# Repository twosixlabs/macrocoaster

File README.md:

# Macrocoaster

Thank you for picking up a macrocoaster from TwoSix Technologies!

If you weren't able to pick one up in person, [this repo](./hardware/PCB/) contains mainufacturing files to order your own board (through JLCPCB, PCBWAY, etc.)

## Why this?
We wanted to give you something useful, fun, and memorable, whether it's a neat circuit board coaster, a fun beginner-friendly soldering kit, or a powerful productivity tool :)

## Usage
The Macrocoaster has two main uses: as a coaster, and as a macropad!
### Coaster:

* Coaster 👍
### Macropad:

* A "macropad" is a (usually) small keyboard used to add functionality to or automate your regular keyboard. Each key's function is programmable, so on a press it can type entire paragraphs, change your computer volume, or hit a combination of keys together. 

* The macrocoaster is unique in that there is a knob that lets you scroll through [layers](https://keebmaker.com/pages/layers), allowing for "pages" of macro keys, instead of just 11. You can think of this like how your SHIFT key changes certain keyboard keys to something else, but instead of one modifier key (SHIFT), you have a dial!

## Feature Overview
### Hardware
* Ruler
    * Inch and mm ruler
    * Common trace widths
    * Common hole diameters
* Header references
    * Common header pitches for reference
* Cross-microcontroller compatibility
    * The macrocoaster board can use an [Arduino Pro Micro](https://www.aliexpress.us/item/3256805735375493.html), [Elite-C](https://www.boardsource.xyz/products/Elite-C_v4), [kb2040](https://www.adafruit.com/product/5302) or any other pro-micro-esque footprint board [supported by QMK](https://github.com/qmk/qmk_firmware/blob/master/docs/compatible_microcontrollers.md)
* ENIG finish - there's gold on this board! 😱
### Software
* Scrollable layers
    * The left rotary encoder scrolls through defined keyboard layers (displayed on the OLED) for a theoretical maximum of (32 layers) * (11 keys) = *_352_ custom macro keys*!
* Bindable rotary encoder
    * By default, the right rotary encoder functions as a volume knob, but can be rebound to send any keycode! (for example, scrolling the grid size in KiCAD)
* Caps-lock indicator via OLED

## BoM (Bill of Materials)
See the [interactive BoM](https://htmlpreview.github.io/?https://github.com/twosixlabs/macrocoaster/blob/main/hardware/BoM/ibom.html) :)
<!-- Note: Update link to future repo! -->

#### Required:
* Microcontroller (see [above](#hardware))
* Any full-size [Cherry MX](https://www.keychron.com/blogs/news/cherry-mechanical-switch-guide) style [keyswitches](https://www.theremingoat.com/blog/beginners-guide) work 
    * Personally, [these](https://drop.com/buy/everglide-oreo-mechanical-switches) and [these](https://divinikey.com/products/lelelab-y2k-tactile-switches) are my favorite
* I recommend [EC-11 style rotary encoders](https://www.amazon.com/uxcell-Degree-Encoder-Digital-Potentiometer/dp/B07R8JPM6D)
* I used [these diodes](https://www.amazon.com/BOJACK-Switching-IN4148-Electronic-Silicon/dp/B07Q4F3Y5W)
* Any 128x64 `SSD1306` OLED breakout with a `[GND, Vcc, SCL, SDA]` pinout works
    * I used [these](https://www.amazon.com/Hosyond-Display-Self-Luminous-Compatible-Raspberry/dp/B09C5K91H7) as the yellow lines make the layer name stand out nicely :D

#### Optional: (but highly recommended)
* Keycaps
    * Entirely your preference :)
        * [This site](https://kbdfans.com/collections/keycaps) is a great starting point
            * Check if there is a "numpad" set, if you don't want the whole keyboard
            * Sites such as [this](https://www.wasdkeyboards.com/products/keycaps/blank-keycap-singles.html) offer per-key pricing, some other sites can even print custom designs on keys!
* Rotary encoder knobs
    * There are many, many [options](https://www.amazon.com/s?k=potentiometer+knob), just make sure they fit your encoder shaft (some are semi-circles, some have knurling, etc.)
* [Rubber "feet"](https://www.amazon.com/s?k=rubber+feet)
    * This keeps the bottom of the board (with the solder blobs/THT components) from scratching up or shorting on whatever surface you have.

## Assembly
1. Liberally apply flux to the back of the board (the side with all the graphics)
2. Place your key switches (`SW1` - `SW11`) in (on the side without the rules), and solder them
3. Diodes (technically optional, if you don't care about [ghosting](https://pcbheaven.com/wikipages/How_Key_Matrices_Works/))
    * If using diodes, solder down `D1` - `D11` (in any order). Make sure the polarity is correct.
    * If not using diodes, short `D1` - `D11` with solder, wires, or leads
4. Solder both rotary encoders (`SW13`, `SW14`)
5. Solder down your controller
    * You can use the castellated pads if your controller has them, or simply use traditional headers
6. Head down to the [Programming guide](#programming) before soldering the OLED
7. Apply some kapton (or other non-conductive tape) to the bottom of the OLED
    * This prevents the OLED from shorting microcontroller pins
8. Solder down the OLED so it covers your controller
    * Note: if using headers (instead of castellated pads) to solder down your controller, you made need [tall headers](https://www.amazon.com/HiLetgo-20pcs-2-54mm-Single-Header/dp/B07R5QDL8D) or [female headers](https://www.amazon.com/Glarks-Connector-Assortment-Stackable-Breakaway/dp/B07CWSXY7P) to clear the board.
        * In the case of the kb2040, the stemma connector causes the OLED to sit at a bit of an angle, which personally I find kind of convenient.

## Programming
1. Install `qmk`
    * [QMK install guide](https://docs.qmk.fm/#/newbs_building_firmware)
        * Note: Merging the macrocoaster into qmk is underway.
        * For now
          * Define a new keyboard `qmk new-keyboard`
          * Choose last option `none of the above`
          * Choose your chip, although it doesn't matter. I selected `kb2040`
2. Download the code
    * `git clone https://github.com/twosixtech/macrocoaster && cd macrocoaster/firmware`
3. Compile and flash for your microcontroller
    * You will need to press the Flash/boot/etc. button down when loading the code for the first time (QMK will prompt you ) 
        * All later flashes can be done with the [magic-bootloader](https://github.com/qmk/qmk_firmware/blob/master/docs/feature_bootmagic.md) key :)
     * delete everything in the macrocoaster dir defined with `qmk new-keyboard` above
     * copy   `macrocoaster/firmware` into your qmk home dir and difined firmware for macrocoaster `qmk_firmware/keyboards/macrocoaster`. Like this `cp -r * ~/qmk_firmware/keyboards/macrocoaster` or similar.
    * Elite-C/Pro-micro
        * `qmk compile -kb macrocoaster -km default && qmk flash -bl dfu -km default -kb macrocoaster`
    * kb2040
        * `qmk compile -kb macrocoaster -km default && qmk flash -km default -kb macrocoaster -e CONVERT_TO=kb2040`

## Macropad Usage
By default, the macropad comes with (roughly) [this layout](./firmware/keymaps/default/keymap.c):

# Notes
To put the KB2040 into programming mode, with the USB port oriented up, hold the bottom left button down, and then press the right and release the left. As documented [here](https://golem.hu/guide/kmk-firmware/)

## Customization (WIP)
Almost all customization will be done in the [`keymap.c`](./firmware/keymaps/default/keymap.c) file.

See the [QMK docs](https://docs.qmk.fm/#/) and [QMK code](https://github.com/qmk/qmk_firmware/blob/master/docs/) for instructions/guidance, as well as the comments in `keymap.c`.
* If you toss the code, with its existing comments into ChatGPT, it does a pretty good job at helping explain :)

The bootloader can be entered by holding down the `SW4` key while the board is powered on
* Note: with the `kb2040`, entering the bootloader make take a few attempts (make sure to wait ~5s on each attempt)

_Note_: Unfortunately because of QMK is architected with macros and `#define`'s, values for things like layer #'s must be known at compile-time and not runtime, making things like automatically calculating the next/prev layer very difficult :(
For example, 
```
#define NUMBER_OF_LAYERS (sizeof(keymaps) / sizeof(keymaps[0]))

int get_next_layer(int currlayer) {
    return (currlayer + 1) % NUMBER_OF_LAYERS;
}
int get_prev_layer(int currlayer) {
    return (currlayer - 1 + NUMBER_OF_LAYERS) % NUMBER_OF_LAYERS;
}
```
is not possible. </a>

## Cases
STL/3MF files for 3D-printable cases can be found in the [cases](./hardware/Cases) folder :)

## Builds
If you feel inclined, it would be amazing if if/after you complete a macrocoaster build, you post it in the [builds](./builds) folder! I posted [my build(s)](./builds/Engineer-2) there, feel free to copy that folder and use it as a template :)

If you want to share your build, please open a PR with your setup in its own subfolder in the builds folder!

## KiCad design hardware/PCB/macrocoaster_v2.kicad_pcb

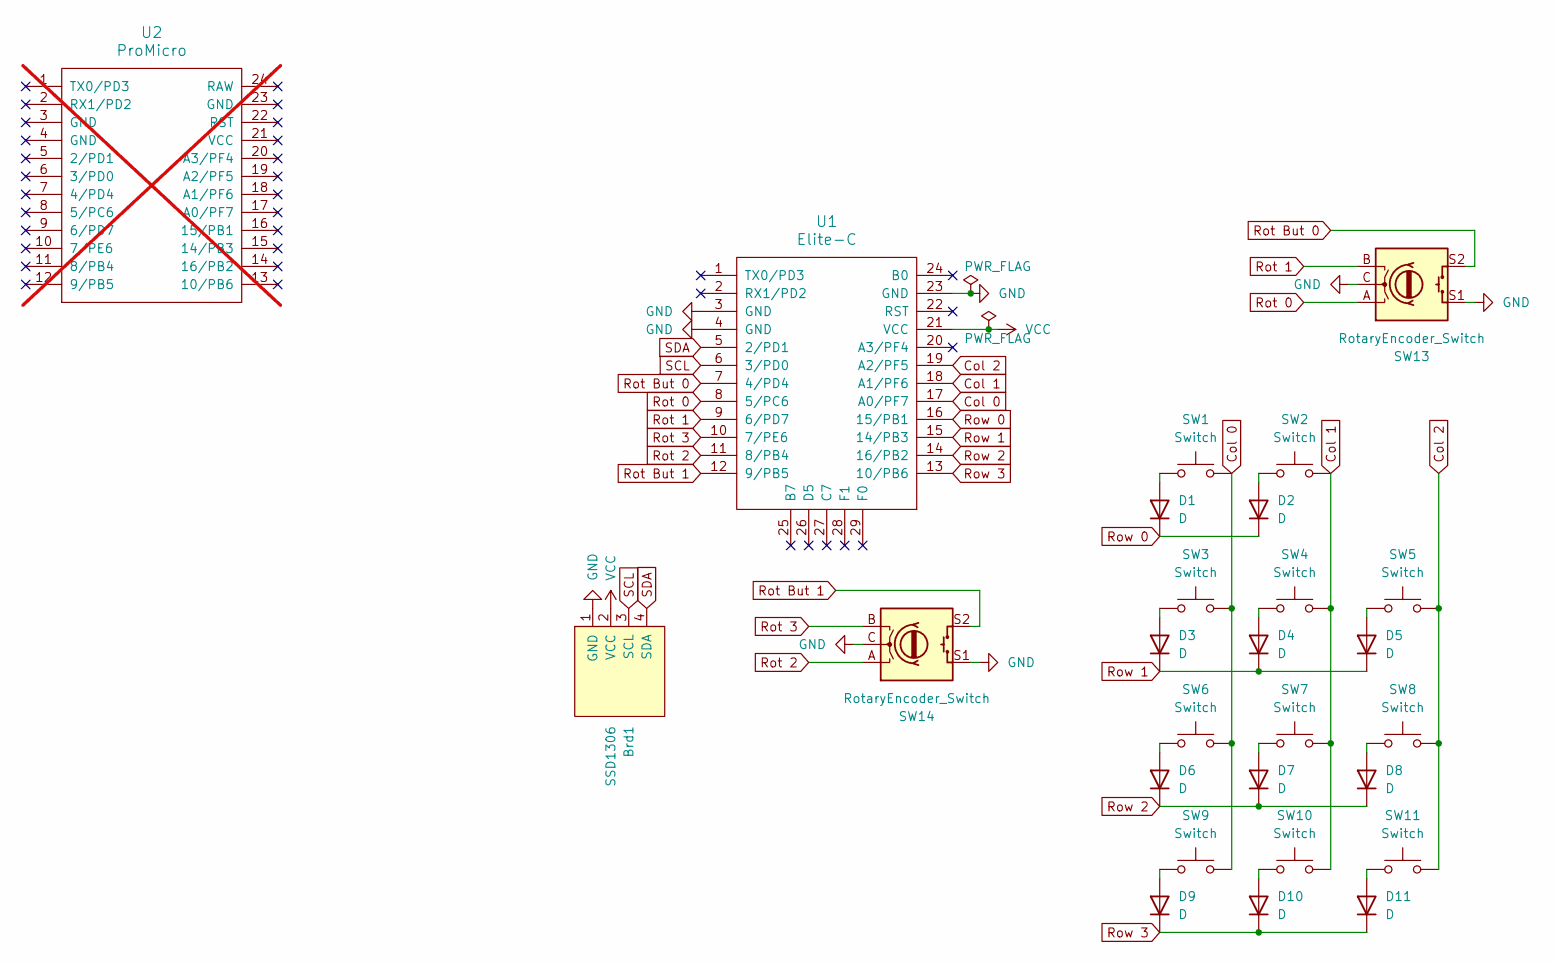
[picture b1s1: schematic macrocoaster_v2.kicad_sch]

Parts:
Brd1: SSD1306; 128x64OLED
D1, D2, D3, D4, D5, D6, D7, D8, D9, D10, D11: D; D_SOD123_axial
SW1, SW2, SW3, SW4, SW5, SW6, SW7, SW8, SW9, SW10, SW11: Switch; MX_PCB_1.00u
SW13, SW14: RotaryEncoder_Switch; RotaryEncoder_Alps_EC11E-Switch_Vertical_H20mm
U1: Elite-C; Elite-C-castellated-29pin-holes
U2: ProMicro; not fitted

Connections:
Col 0: SW1.2, SW3.2, SW6.2, SW9.2, U1.17 (A0/PF7)
Col 1: SW2.2, SW4.2, SW7.2, SW10.2, U1.18 (A1/PF6)
Col 2: SW5.2, SW8.2, SW11.2, U1.19 (A2/PF5)
GND: Brd1.1 (GND), SW13.C, SW13.S1, SW14.C, SW14.S1, U1.3 (GND), U1.4 (GND), U1.23 (GND)
unnamed: D1.2 (A), SW1.1
unnamed: D2.2 (A), SW2.1
unnamed: D3.2 (A), SW3.1
unnamed: D4.2 (A), SW4.1
unnamed: D5.2 (A), SW5.1
unnamed: D6.2 (A), SW6.1
unnamed: D7.2 (A), SW7.1
unnamed: D8.2 (A), SW8.1
unnamed: D9.2 (A), SW9.1
unnamed: D10.2 (A), SW10.1
unnamed: D11.2 (A), SW11.1
Rot 0: SW13.A, U1.8 (5/PC6)
Rot 1: SW13.B, U1.9 (6/PD7)
Rot 2: SW14.A, U1.11 (8/PB4)
Rot 3: SW14.B, U1.10 (7/PE6)
Rot But 0: SW13.S2, U1.7 (4/PD4)
Rot But 1: SW14.S2, U1.12 (9/PB5)
Row 0: D1.1 (K), D2.1 (K), U1.16 (15/PB1)
Row 1: D3.1 (K), D4.1 (K), D5.1 (K), U1.15 (14/PB3)
Row 2: D6.1 (K), D7.1 (K), D8.1 (K), U1.14 (16/PB2)
Row 3: D9.1 (K), D10.1 (K), D11.1 (K), U1.13 (10/PB6)
SCL: Brd1.3 (SCL), U1.6 (3/PD0)
SDA: Brd1.4 (SDA), U1.5 (2/PD1)
VCC: Brd1.2 (VCC), U1.21 (VCC)

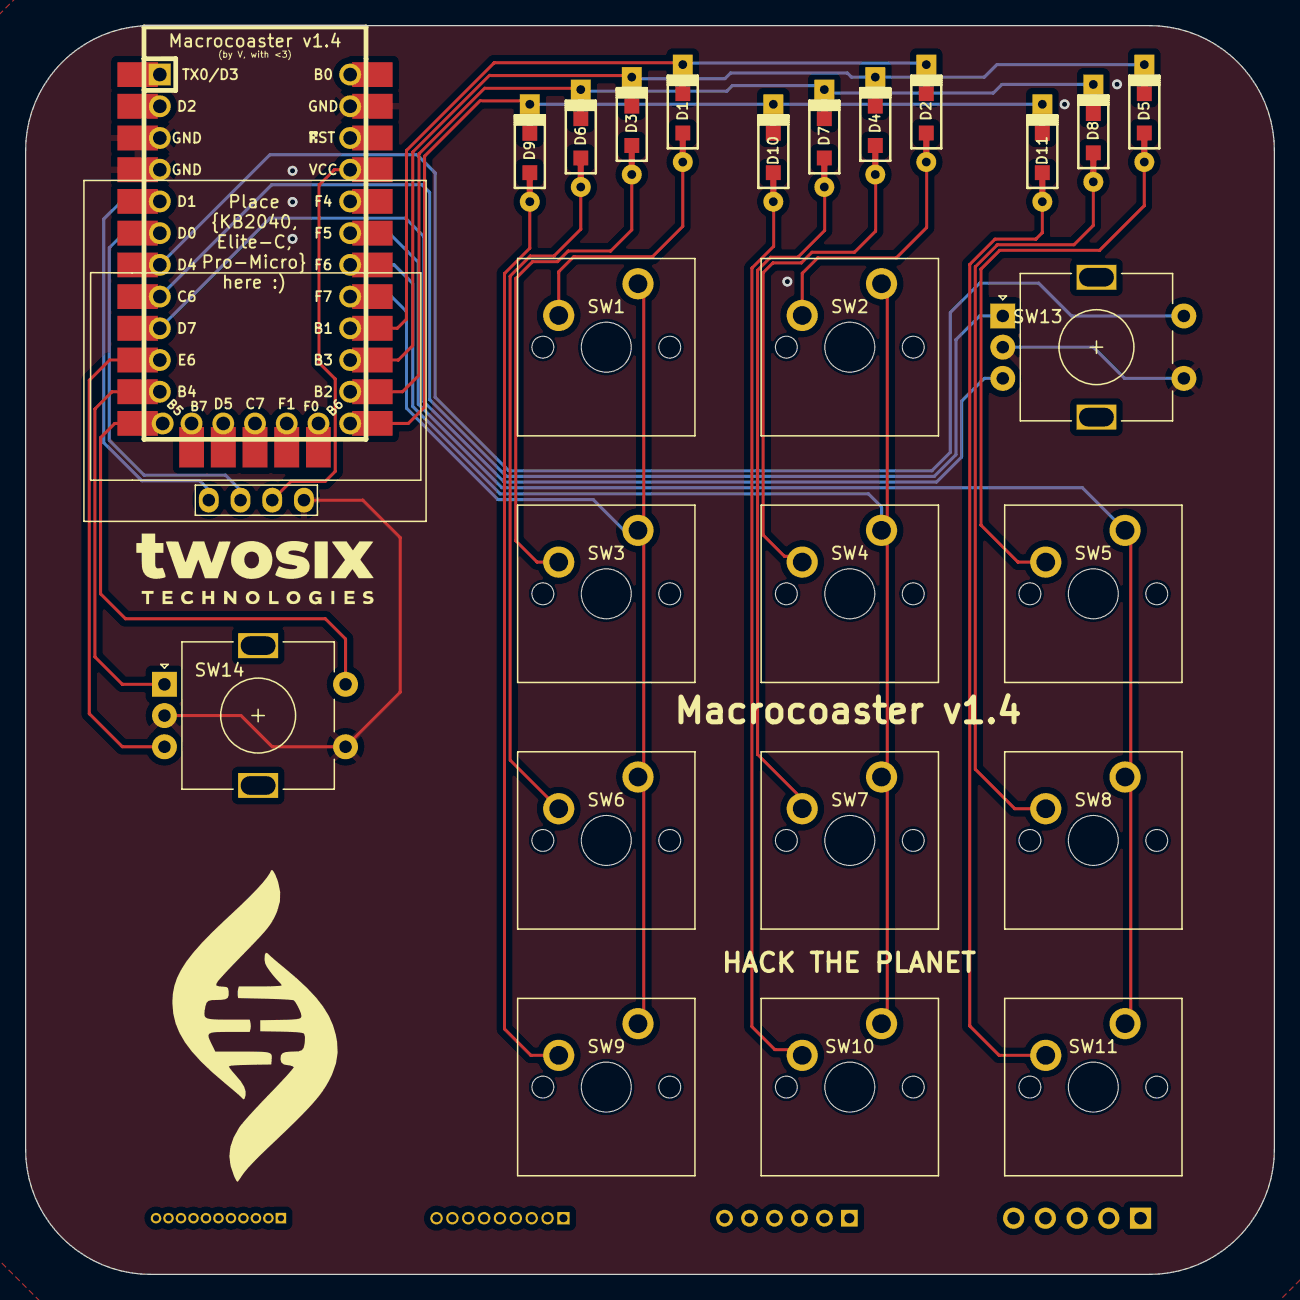
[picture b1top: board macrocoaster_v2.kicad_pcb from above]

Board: 2 copper layers, 100.0 x 100.0 mm, 26 parts (0 on the bottom side), 28 nets.

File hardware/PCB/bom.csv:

Designator,Footprint,Quantity,Value,LCSC Part #
Brd1,128x64OLED,1,SSD1306,
"D1, D10, D11, D2, D3, D4, D5, D6, D7, D8, D9",D_SOD123_axial,11,D,
"SW1, SW10, SW11, SW2, SW3, SW4, SW5, SW6, SW7, SW8, SW9",MX_PCB_1.00u,11,Switch,
"SW13, SW14",RotaryEncoder_Alps_EC11E-Switch_Vertical_H20mm,2,RotaryEncoder_Switch,
U1,Elite-C-castellated-29pin-holes,1,Elite-C,

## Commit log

2024-01-09 published
2024-01-09 prod release
2024-01-09 prod release links
2024-01-17 added builds and cases
2024-01-17 added case info
2024-06-03 updated kicad version
2024-06-03 Updated manufacturing files
2024-06-03 updated PCB files
